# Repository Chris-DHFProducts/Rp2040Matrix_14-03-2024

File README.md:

Notes: 
  The hardware and software is compatable with older board dated 02-21-2024.
  PBC files are saved with KiCad V8.0.1

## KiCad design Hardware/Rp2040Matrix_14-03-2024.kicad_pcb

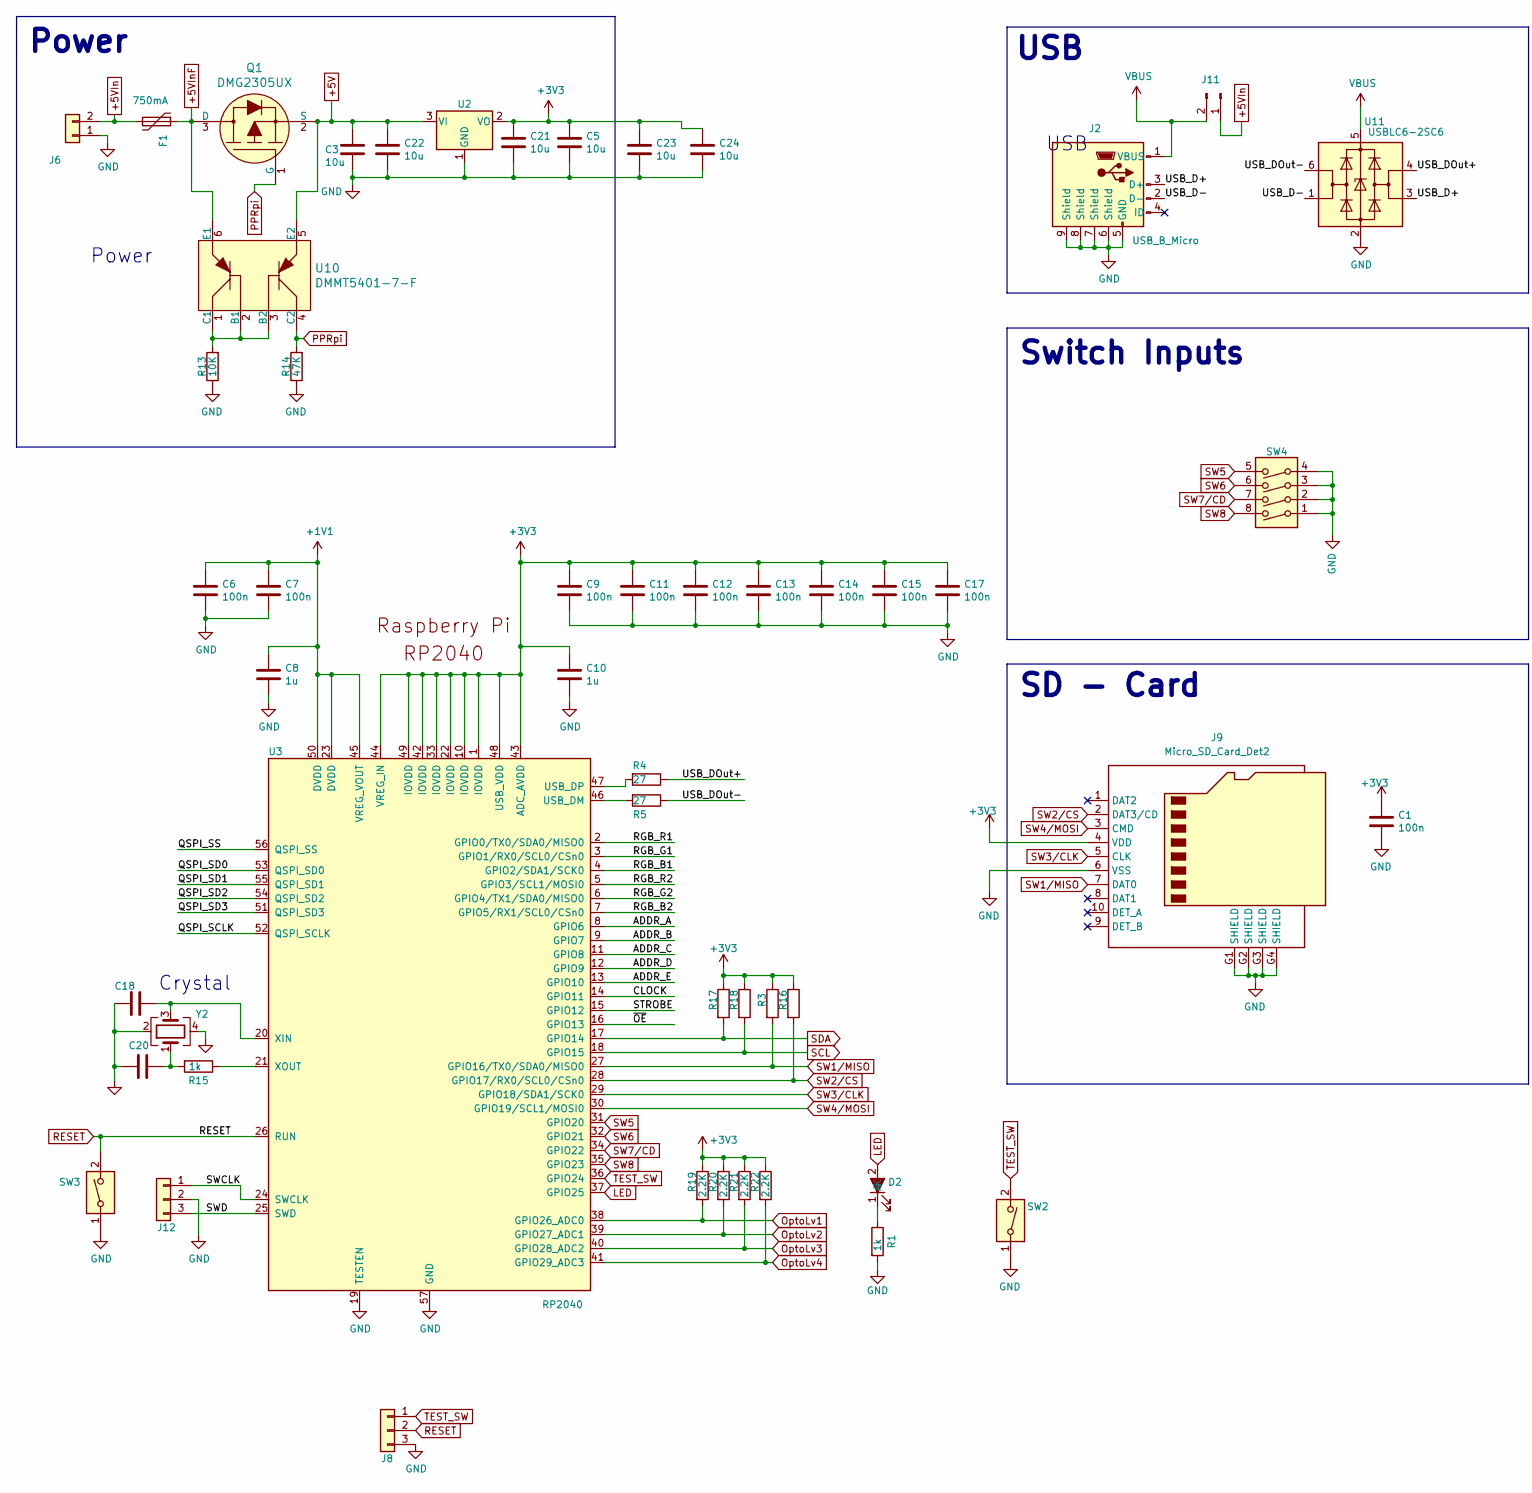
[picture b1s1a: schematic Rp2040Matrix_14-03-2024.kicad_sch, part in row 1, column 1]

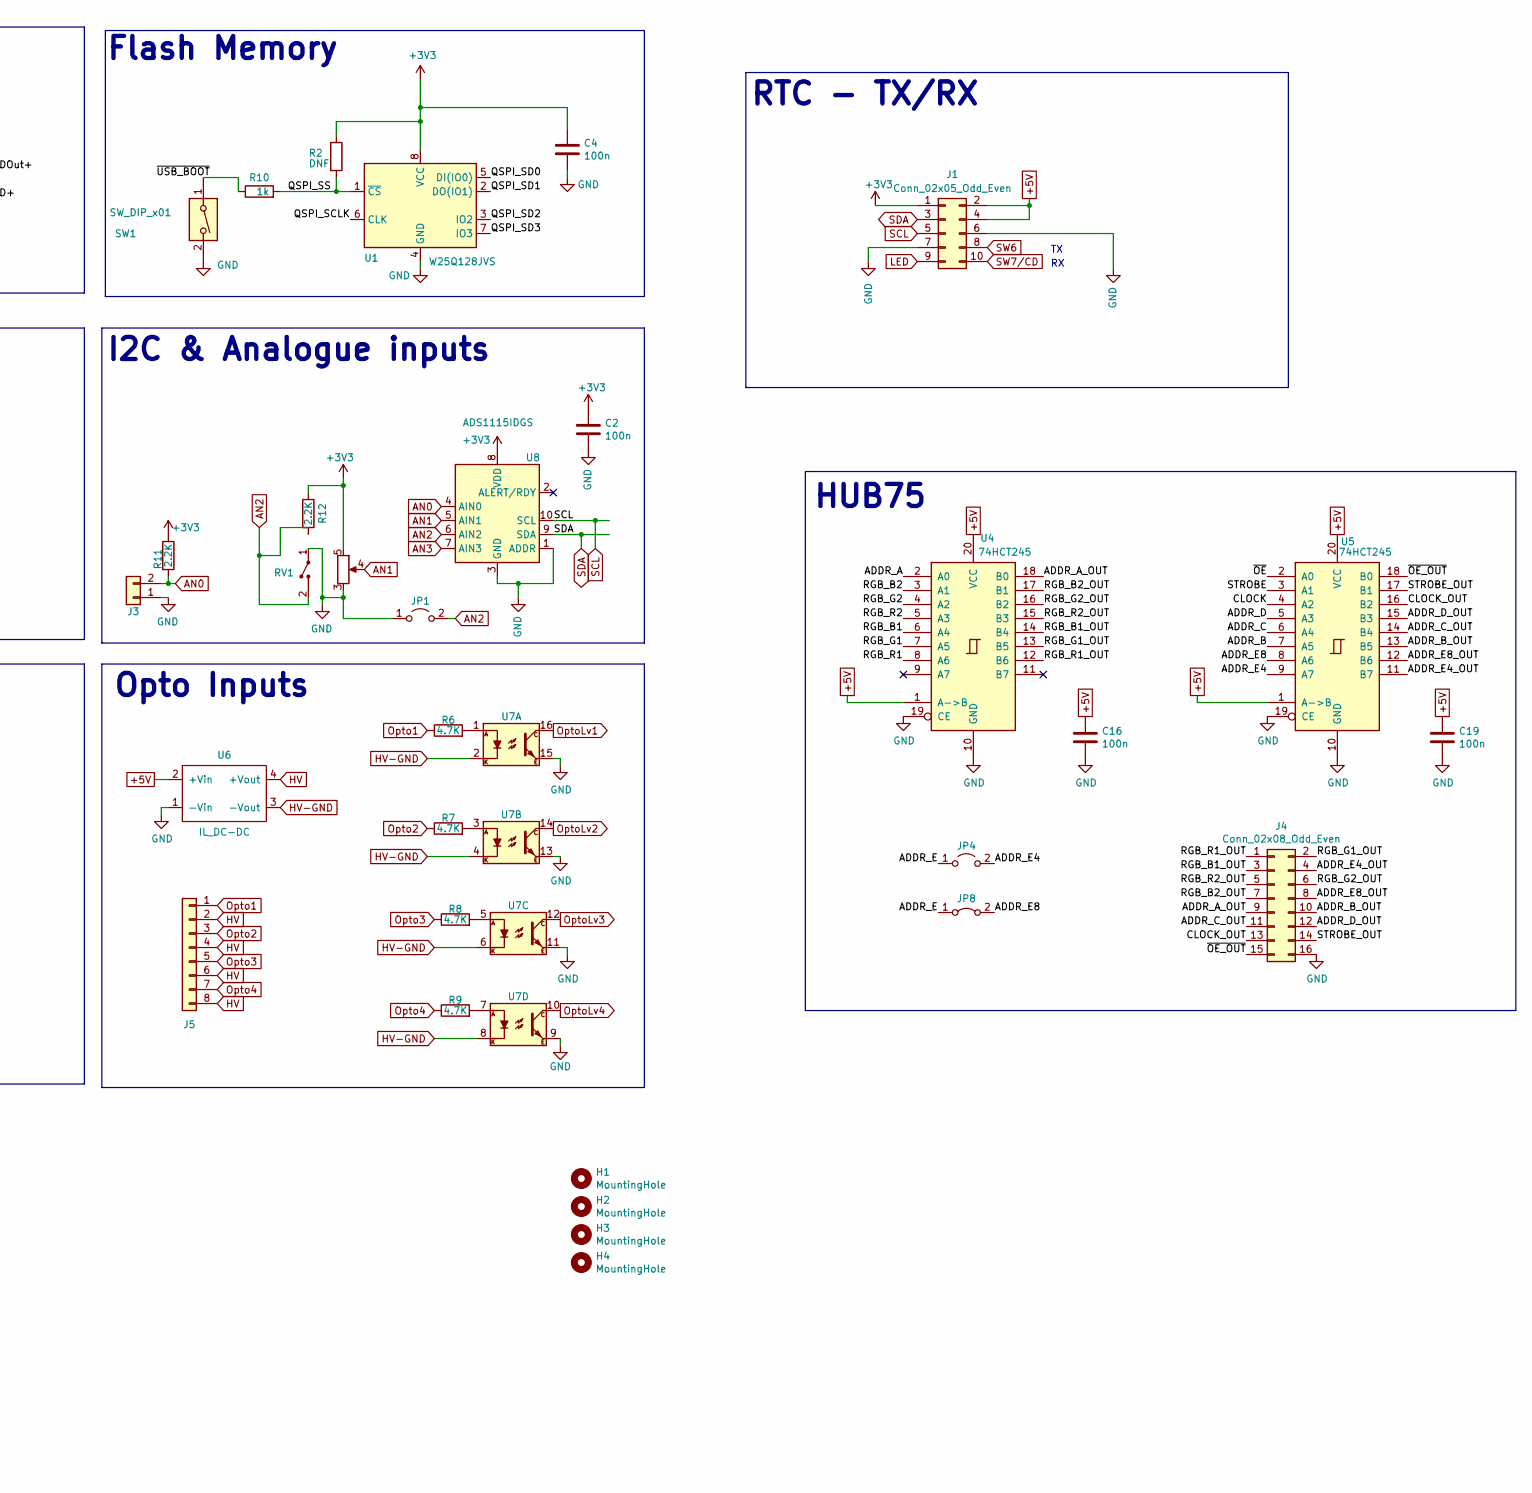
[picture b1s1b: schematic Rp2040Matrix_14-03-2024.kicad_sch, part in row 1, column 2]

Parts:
C1, C2, C4, C6, C7, C9, C11, C12, C13, C14, C15, C16, C17, C19: 100n; C_0402_1005Metric; MPN CL05B104KO5NNNC; LCSC C1525
C3, C5, C21, C22, C23, C24: 10u; C_0805_2012Metric; MPN CL21A106KAYNNNE; LCSC C15850
C8, C10: 1u; C_0402_1005Metric; MPN CL05A105KA5NQNC; LCSC C52923
C18, C20: 30p; C_0402_1005Metric; MPN 0402CG300F500NT; LCSC C913871
D2: Red LED 0603; LED0603-R-RD; MPN NCD0603R1; LCSC C84263
F1: 750mA; Fuse_1812_4532Metric; MPN BSMD1812-075-33V; LCSC C883146
H1, H2, H3, H4: MountingHole; MountingHole_3.2mm_M3
J1: Conn_02x05_Odd_Even; PinHeader_2x05_P2.54mm_Vertical
J2: USB_B_Micro; MICRO-USB-SMD_MICRO-USB-A17; MPN U-F-M5DD-W-2; LCSC C145793
J3, J6: Conn_01x02_Male; TerminalBlock_Phoenix_PT-1,5-2-3.5-H_1x02_P3.50mm_Horizontal; MPN DB125-3.5-2P-GN-S; LCSC C466970
J4: Conn_02x08_Odd_Even; IDC-Header_2x08_P2.54mm_Vertical; MPN 321016SG0ABK00A01; LCSC C429960
J5: Conn_01x08_Male; TerminalBlock_Phoenix_PT-1,5-8-3.5-H_1x08_P3.50mm_Horizontal; MPN DB125-3.5-8P-GN-S; LCSC C5184954
J8, J12: Conn_01x03_Male; PinHeader_1x03_P2.54mm_Vertical; MPN 12251103CNG0S115001; LCSC C429954
J9: Micro_SD_Card_Det2; MOLEX_104031-0811; MPN 1040310811; LCSC C585350
J11: Conn_01x02_Male; PinHeader_1x02_P2.54mm_Vertical; MPN PH-01078; LCSC Liansheng
JP1, JP4: Jumper_2_Open; SolderJumper-2_P1.3mm_Open_RoundedPad1.0x1.5mm
JP8: Jumper_2_Bridged; SolderJumper-2_P1.3mm_Bridged_RoundedPad1.0x1.5mm
Q1: DMG2305UX; SOT-23; MPN DMG2305UX-7; LCSC C150470
R1, R10, R15: 1k; R_0402_1005Metric; MPN 0402WGF1001TCE; LCSC C11702
R2: DNF; R_0603_1608Metric
R3, R11, R12, R16, R17, R18, R19, R20, R21, R22: 2.2K; R_0402_1005Metric; MPN 0402WGF2201TCE; LCSC C25879
R4, R5: 27; R_0402_1005Metric; MPN RC0402FR-0727RL; LCSC C138021
R6, R7, R8, R9: 4.7K; R_1206_3216Metric; MPN 1206W4F4701T5E; LCSC C17936
R13: 10K; R_0402_1005Metric; MPN 0402WGF1002TCE; LCSC C25744
R14: 47K; R_0402_1005Metric; MPN 0402WGF4702TCE; LCSC C25792
RV1: R_Pot+SW; AM-Pot_01
SW1, SW2, SW3: SW_DIP_x01; SW-SMD_4P-L5.1-W5.1-P3.70-LS6.5-TL-2; MPN TS-1187A-B-A-B; LCSC C318884
SW4: Conn_01x04_Male; SW_DIP_SPSTx04_Slide_Omron_A6S-410x_W8.9mm_P2.54mm; LCSC C2842911
U1: W25Q128JVS; SOIC-8_5.23x5.23mm_P1.27mm; MPN W25Q128JVSIQ; LCSC C97521
U2: Voltage Regulator Fixed 3.3V; SOT-223-3_TabPin2; MPN AMS1117-3.3; LCSC C6186
U3: RP2040; RP2040-QFN-56; MPN RP2040; LCSC C2040
U4, U5: 74HCT245; TSSOP-20_4.4x6.5mm_P0.65mm; MPN SN74HCT245PWR; LCSC C6779
U6: IL_DC-DC; IL-DC-DC-XP; MPN IE0524S; Farnell 2084318
U7: OPTO-TRANSISTOR-4; SOP-16_L10.3-W4.4-P1.27-LS7.0-BL; MPN TLP291; LCSC C60900
U8: ADS1115IDGS; VSSOP-10_3x3mm_P0.5mm; MPN ADS1115IDGSR; LCSC C37593
U10: DMMT5401-7-F; MPN DMMT5401-7-F; LCSC C154733
U11: USBLC6-2SC6; SOT-23-6; MPN TPUSBLC6-2SC6; LCSC C558442
Y2: Crystal_GND24; Crystal YSX321SL; MPN TX322512M4LBCE2T; LCSC C5182760

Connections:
+1V1: C6.1, C7.1, C8.1, U3.23 (DVDD), U3.45 (VREG_VOUT), U3.50 (DVDD)
+3V3: C1.1, C2.1, C4.1, C5.1, C9.1, C10.1, C11.1, C12.1, C13.1, C14.1, C15.1, C17.1, C21.1, C23.1, C24.1, J1.1, J9.4 (VDD), R2.1, R3.1, R11.1, R12.1, R16.1, R17.1, R18.1, R19.1, R20.1, R21.1, R22.1, RV1.5, U1.8 (VCC), U2.2 (VO), U3.1 (IOVDD), U3.10 (IOVDD), U3.22 (IOVDD), U3.33 (IOVDD), U3.42 (IOVDD), U3.43 (ADC_AVDD), U3.44 (VREG_IN), U3.48 (USB_VDD), U3.49 (IOVDD), U8.8 (VDD)
+5V: C3.1, C16.1, C19.1, C22.1, J1.2, J1.4, Q1.2 (S), U2.3 (VI), U4.1 (A->B), U4.20 (VCC), U5.1 (A->B), U5.20 (VCC), U6.2 (+Vin), U10.5 (E2)
+5VIn: F1.2, J6.2, J11.1
+5VInF: F1.1, Q1.3 (D), U10.6 (E1)
/ADDR_A: U3.8 (GPIO6), U4.2 (A0)
/ADDR_A_OUT: J4.9, U4.18 (B0)
/ADDR_B: U3.9 (GPIO7), U5.7 (A5)
/ADDR_B_OUT: J4.10, U5.13 (B5)
/ADDR_C: U3.11 (GPIO8), U5.6 (A4)
/ADDR_C_OUT: J4.11, U5.14 (B4)
/ADDR_D: U3.12 (GPIO9), U5.5 (A3)
/ADDR_D_OUT: J4.12, U5.15 (B3)
/ADDR_E: JP4.1 (A), JP8.1 (A), U3.13 (GPIO10)
/ADDR_E4: JP4.2 (B), U5.9 (A7)
/ADDR_E4_OUT: J4.4, U5.11 (B7)
/ADDR_E8: JP8.2 (B), U5.8 (A6)
/ADDR_E8_OUT: J4.8, U5.12 (B6)
/CLOCK: U3.14 (GPIO11), U5.4 (A2)
/CLOCK_OUT: J4.13, U5.16 (B2)
/QSPI_SCLK: U1.6 (CLK), U3.52 (QSPI_SCLK)
/QSPI_SD0: U1.5 (DI(IO0)), U3.53 (QSPI_SD0)
/QSPI_SD1: U1.2 (DO(IO1)), U3.55 (QSPI_SD1)
/QSPI_SD2: U1.3 (IO2), U3.54 (QSPI_SD2)
/QSPI_SD3: U1.7 (IO3), U3.51 (QSPI_SD3)
/QSPI_SS: R2.2, R10.2, U1.1 (~CS), U3.56 (QSPI_SS)
/RGB_B1: U3.4 (GPIO2/SDA1/SCK0), U4.6 (A4)
/RGB_B1_OUT: J4.3, U4.14 (B4)
/RGB_B2: U3.7 (GPIO5/RX1/SCL0/CSn0), U4.3 (A1)
/RGB_B2_OUT: J4.7, U4.17 (B1)
/RGB_G1: U3.3 (GPIO1/RX0/SCL0/CSn0), U4.7 (A5)
/RGB_G1_OUT: J4.2, U4.13 (B5)
/RGB_G2: U3.6 (GPIO4/TX1/SDA0/MISO0), U4.4 (A2)
/RGB_G2_OUT: J4.6, U4.16 (B2)
/RGB_R1: U3.2 (GPIO0/TX0/SDA0/MISO0), U4.8 (A6)
/RGB_R1_OUT: J4.1, U4.12 (B6)
/RGB_R2: U3.5 (GPIO3/SCL1/MOSI0), U4.5 (A3)
/RGB_R2_OUT: J4.5, U4.15 (B3)
/STROBE: U3.15 (GPIO12), U5.3 (A1)
/STROBE_OUT: J4.14, U5.17 (B1)
/SWCLK: J12.1, U3.24 (SWCLK)
/SWD: J12.3, U3.25 (SWD)
/USB_D+: J2.3 (D+), U11.3 (I/O2)
/USB_D-: J2.2 (D-), U11.1 (I/O1)
/USB_DOut+: R4.1, U11.4 (I/O2)
/USB_DOut-: R5.1, U11.6 (I/O1)
/~OE_OUT: J4.15, U5.18 (B0)
/~OE: U3.16 (GPIO13), U5.2 (A0)
/~USB_BOOT: R10.1, SW1.1
AN0: J3.2, R11.2, U8.4 (AIN0)
AN1: RV1.4, U8.5 (AIN1)
AN2: JP1.2 (B), RV1.2, U8.6 (AIN2)
AN3: U8.7 (AIN3)
GND: C1.2, C2.2, C3.2, C4.2, C5.2, C6.2, C7.2, C8.2, C9.2, C10.2, C11.2, C12.2, C13.2, C14.2, C15.2, C16.2, C17.2, C18.1, C19.2, C20.1, C21.2, C22.2, C23.2, C24.2, J1.6, J1.7, J2.5 (GND), J2.6 (Shield), J2.7 (Shield), J2.8 (Shield), J2.9 (Shield), J3.1, J4.16, J6.1, J8.3, J9.6 (VSS), J9.G1 (SHIELD), J9.G2 (SHIELD), J9.G3 (SHIELD), J9.G4 (SHIELD), J12.2, JP1.1 (A), R1.2, R13.1, R14.1, RV1.1, RV1.3, SW1.2, SW2.1, SW3.1, SW4.1, SW4.2, SW4.3, SW4.4, U1.4 (GND), U2.1 (GND), U3.19 (TESTEN), U3.57 (GND), U4.10 (GND), U4.19 (CE), U5.10 (GND), U5.19 (CE), U6.1 (-Vin), U7.9, U7.11, U7.13, U7.15, U8.1 (ADDR), U8.3 (GND), U11.2 (GND), Y2.2, Y2.4
HV: J5.2, J5.4, J5.6, J5.8, U6.4 (+Vout)
HV-GND: U6.3 (-Vout), U7.2, U7.4, U7.6, U7.8
LED: D2.2 (A), J1.9, U3.37 (GPIO25)
unnamed: C20.2, R15.2, Y2.1
unnamed: D2.1 (K), R1.1
unnamed: R6.2, U7.1
unnamed: R7.2, U7.3
unnamed: R8.2, U7.5
unnamed: R9.2, U7.7
unnamed: R5.2, U3.46 (USB_DM)
unnamed: R4.2, U3.47 (USB_DP)
unnamed: C18.2, U3.20 (XIN), Y2.3
unnamed: R15.1, U3.21 (XOUT)
unnamed: R13.2, U10.1 (C1), U10.2 (B1), U10.3 (B2)
Opto1: J5.1, R6.1
Opto2: J5.3, R7.1
Opto3: J5.5, R8.1
Opto4: J5.7, R9.1
OptoLv1: R19.2, U3.38 (GPIO26_ADC0), U7.16
OptoLv2: R20.2, U3.39 (GPIO27_ADC1), U7.14
OptoLv3: R21.2, U3.40 (GPIO28_ADC2), U7.12
OptoLv4: R22.2, U3.41 (GPIO29_ADC3), U7.10
PPRpi: Q1.1 (G), R14.2, U10.4 (C2)
RESET: J8.2, SW3.2, U3.26 (RUN)
SCL: J1.5, R18.2, U3.18 (GPIO15), U8.10 (SCL)
SDA: J1.3, R17.2, U3.17 (GPIO14), U8.9 (SDA)
SW1/MISO: J9.7 (DAT0), R3.2, U3.27 (GPIO16/TX0/SDA0/MISO0)
SW2/CS: J9.2 (DAT3/CD), R16.2, U3.28 (GPIO17/RX0/SCL0/CSn0)
SW3/CLK: J9.5 (CLK), U3.29 (GPIO18/SDA1/SCK0)
SW4/MOSI: J9.3 (CMD), U3.30 (GPIO19/SCL1/MOSI0)
SW5: SW4.5, U3.31 (GPIO20)
SW6: J1.8, SW4.6, U3.32 (GPIO21)
SW7/CD: J1.10, SW4.7, U3.34 (GPIO22)
SW8: SW4.8, U3.35 (GPIO23)
TEST_SW: J8.1, SW2.2, U3.36 (GPIO24)
VBUS: J2.1 (VBUS), J11.2, U11.5 (VBUS)

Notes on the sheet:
Power
Switch Inputs
I2C & Analogue inputs
SD - Card
Opto Inputs
HUB75
USB
Flash Memory
RTC - TX/RX
Crystal

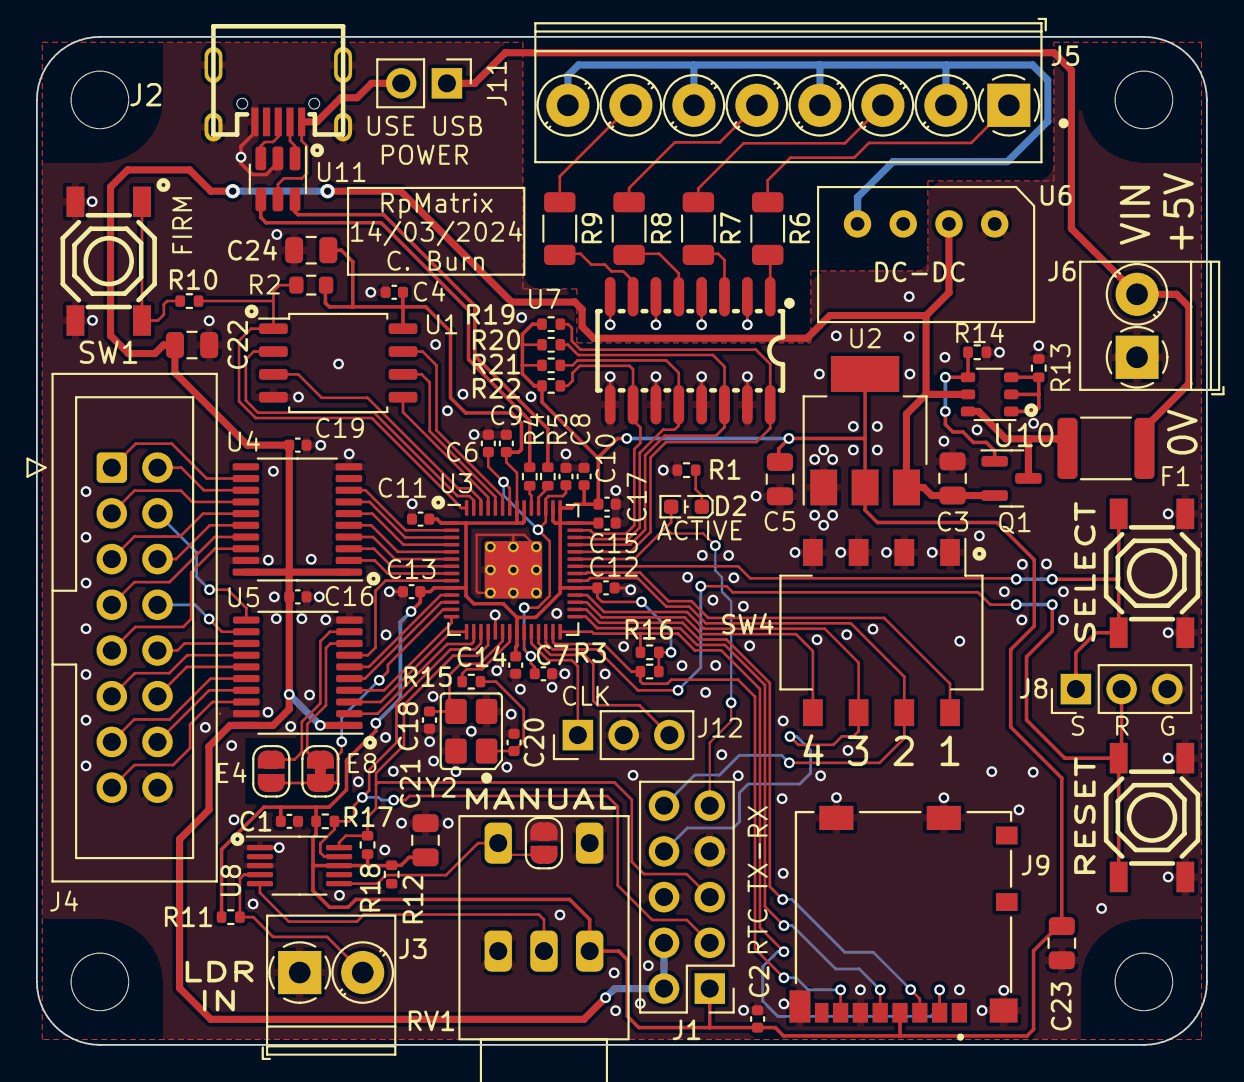
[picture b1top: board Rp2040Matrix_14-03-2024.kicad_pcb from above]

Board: 2 copper layers, 65.0 x 56.0 mm, 82 parts (0 on the bottom side), 89 nets.

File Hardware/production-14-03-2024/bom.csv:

Designator,Footprint,Quantity,Value,LCSC Part #
"C1, C11, C12, C13, C14, C15, C16, C17, C19, C2, C4, C6, C7, C9",0402,14,100n,C1525
"C10, C8",0402,2,1u,C52923
"C18, C20",0402,2,30p,C913871
"C21, C22, C23, C24, C3, C5",0805,6,10u,C15850
D2,LED0603-R-RD,1,Red LED 0603,C84263
F1,1812,1,750mA,C883146
"H1, H2, H3, H4",MountingHole_3.2mm_M3,4,MountingHole,-
J1,PinHeader_2x05_P2.54mm_Vertical,1,Conn_02x05_Odd_Even,
J11,PinHeader_1x02_P2.54mm_Vertical,1,Conn_01x02_Male,Liansheng
"J12, J8",PinHeader_1x03_P2.54mm_Vertical,2,Conn_01x03_Male,C429954
J2,MICRO-USB-SMD_MICRO-USB-A17,1,USB_B_Micro,C145793
"J3, J6","TerminalBlock_Phoenix_PT-1,5-2-3.5-H_1x02_P3.50mm_Horizontal",2,Conn_01x02_Male,C466970
J4,IDC-Header_2x08_P2.54mm_Vertical,1,Conn_02x08_Odd_Even,C429960
J5,"TerminalBlock_Phoenix_PT-1,5-8-3.5-H_1x08_P3.50mm_Horizontal",1,Conn_01x08_Male,C5184954
J9,MOLEX_104031-0811,1,Micro_SD_Card_Det2,C585350
"JP1, JP4",SolderJumper-2_P1.3mm_Open_RoundedPad1.0x1.5mm,2,Jumper_2_Open,-
JP8,SolderJumper-2_P1.3mm_Bridged_RoundedPad1.0x1.5mm,1,Jumper_2_Bridged,-
Q1,SOT-23,1,DMG2305UX,C150470
"R1, R10, R15",0402,3,1k,C11702
"R11, R12, R16, R17, R18, R19, R20, R21, R22, R3",0402,10,2.2K,C25879
R13,0402,1,10K,C25744
R14,0402,1,47K,C25792
R2,0603,1,DNF,-
"R4, R5",0402,2,27,C138021
"R6, R7, R8, R9",1206,4,4.7K,C17936
RV1,AM-Pot_01,1,R_Pot+SW,-
"SW1, SW2, SW3",SW-SMD_4P-L5.1-W5.1-P3.70-LS6.5-TL-2,3,SW_DIP_x01,C318884
SW4,SW_DIP_SPSTx04_Slide_Omron_A6S-410x_W8.9mm_P2.54mm,1,Conn_01x04_Male,C2842911
U1,SOIC-8_5.23x5.23mm_P1.27mm,1,W25Q128JVS,C97521
U10,DMMT5401-7-F,1,DMMT5401-7-F,C154733
U11,SOT-23-6,1,USBLC6-2SC6,C558442
U2,SOT-223-3_TabPin2,1,Voltage Regulator Fixed 3.3V,C6186
U3,RP2040-QFN-56,1,RP2040,C2040
"U4, U5",TSSOP-20_4.4x6.5mm_P0.65mm,2,74HCT245,C6779
U6,IL-DC-DC-XP,1,IL_DC-DC,-
U7,SOP-16_L10.3-W4.4-P1.27-LS7.0-BL,1,OPTO-TRANSISTOR-4,C60900
U8,VSSOP-10_3x3mm_P0.5mm,1,ADS1115IDGS,C37593
Y2,Crystal YSX321SL,1,Crystal_GND24,C5182760

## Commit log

2024-03-17 Production copy of PR2040 Matrix Tile Driver
    14-03-2024 production copy of PR2040 Matrix Tile Driver
2024-03-17 README.md
2024-03-17 Hidden files
2024-03-17 Zipped git files
